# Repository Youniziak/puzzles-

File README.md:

# Chaîne « puzzle » — Exylia Project

Concevoir des cartes électroniques sans la vue : la carte est découpée en blocs par fonction, chaque bloc est routé par EasyGerber, puis la chaîne recolle et vérifie le tout avec des logiciels maintenus (KiCad 10, Freerouting, KiKit…). Elle produit aussi de quoi toucher la carte avant de la commander : plan sur papier gonflé, maquette, boîtier et banc de test à imprimer en 3D.

Dépôt public depuis le 25/10/2026. La première carte faite avec la chaîne est la radio RADIONÉO v4. Pour les questions et les idées : l'onglet Discussions.

- `METHODE-CARTES-PUZZLE.md` : la méthode, ce qui a été appris, et l'historique des versions.
- `POUR-LE-FABLAB.md` : les briques et la colle, pour quelqu'un qui voudrait aider.
- `SKILL-carte-puzzle.md` : les instructions pour l'IA qui conduit la chaîne. C'est du texte simple : chacun prend l'IA qu'il veut, libre ou non, du moment qu'elle sait lire des fichiers et lancer des commandes. La chaîne elle-même tourne sans IA. Ces instructions ont été écrites et essayées avec Claude.
- `installer-ubuntu.sh` et `Dockerfile` : pour installer les logiciels.
- `scripts/chaine.py` : la chaîne en une commande.
- `.github/workflows/kicad-happy.yml` : un deuxième avis sur chaque carte, par l'outil libre kicad-happy, à chaque changement.
- `.github/workflows/edea.yml` : un essai de l'outil libre EDeA (bibliothèque partagée de blocs KiCad) : sait-il lire nos fichiers ?

Ne sont pas dans le dépôt : les modèles 3D à imprimer (refaits par la chaîne), les schémas d'autres projets publiés, et la bibliothèque des composants de LCSC/EasyEDA (empreintes, symboles, modèles 3D), que leurs conditions interdisent de republier. Avant la première carte, chacun la télécharge chez soi :

```
python3 outils/telecharger_bibliotheque.py
```

Le script applique ensuite les retouches de la chaîne (`bibliotheque/empreintes/retouches.json`) et vérifie que les pièces n'ont pas changé chez LCSC depuis les cartes déjà faites.

## Licences

Libres et strictes : le logiciel sous GNU AGPL-3.0 (ou plus récente), le matériel (cartes, blocs, maquettes) sous CERN-OHL-S-2.0, les textes sous CC BY-SA 4.0. Le détail, et ce qui vient d'ailleurs : `LICENCE.md`. Les textes des licences : `LICENSES/`.

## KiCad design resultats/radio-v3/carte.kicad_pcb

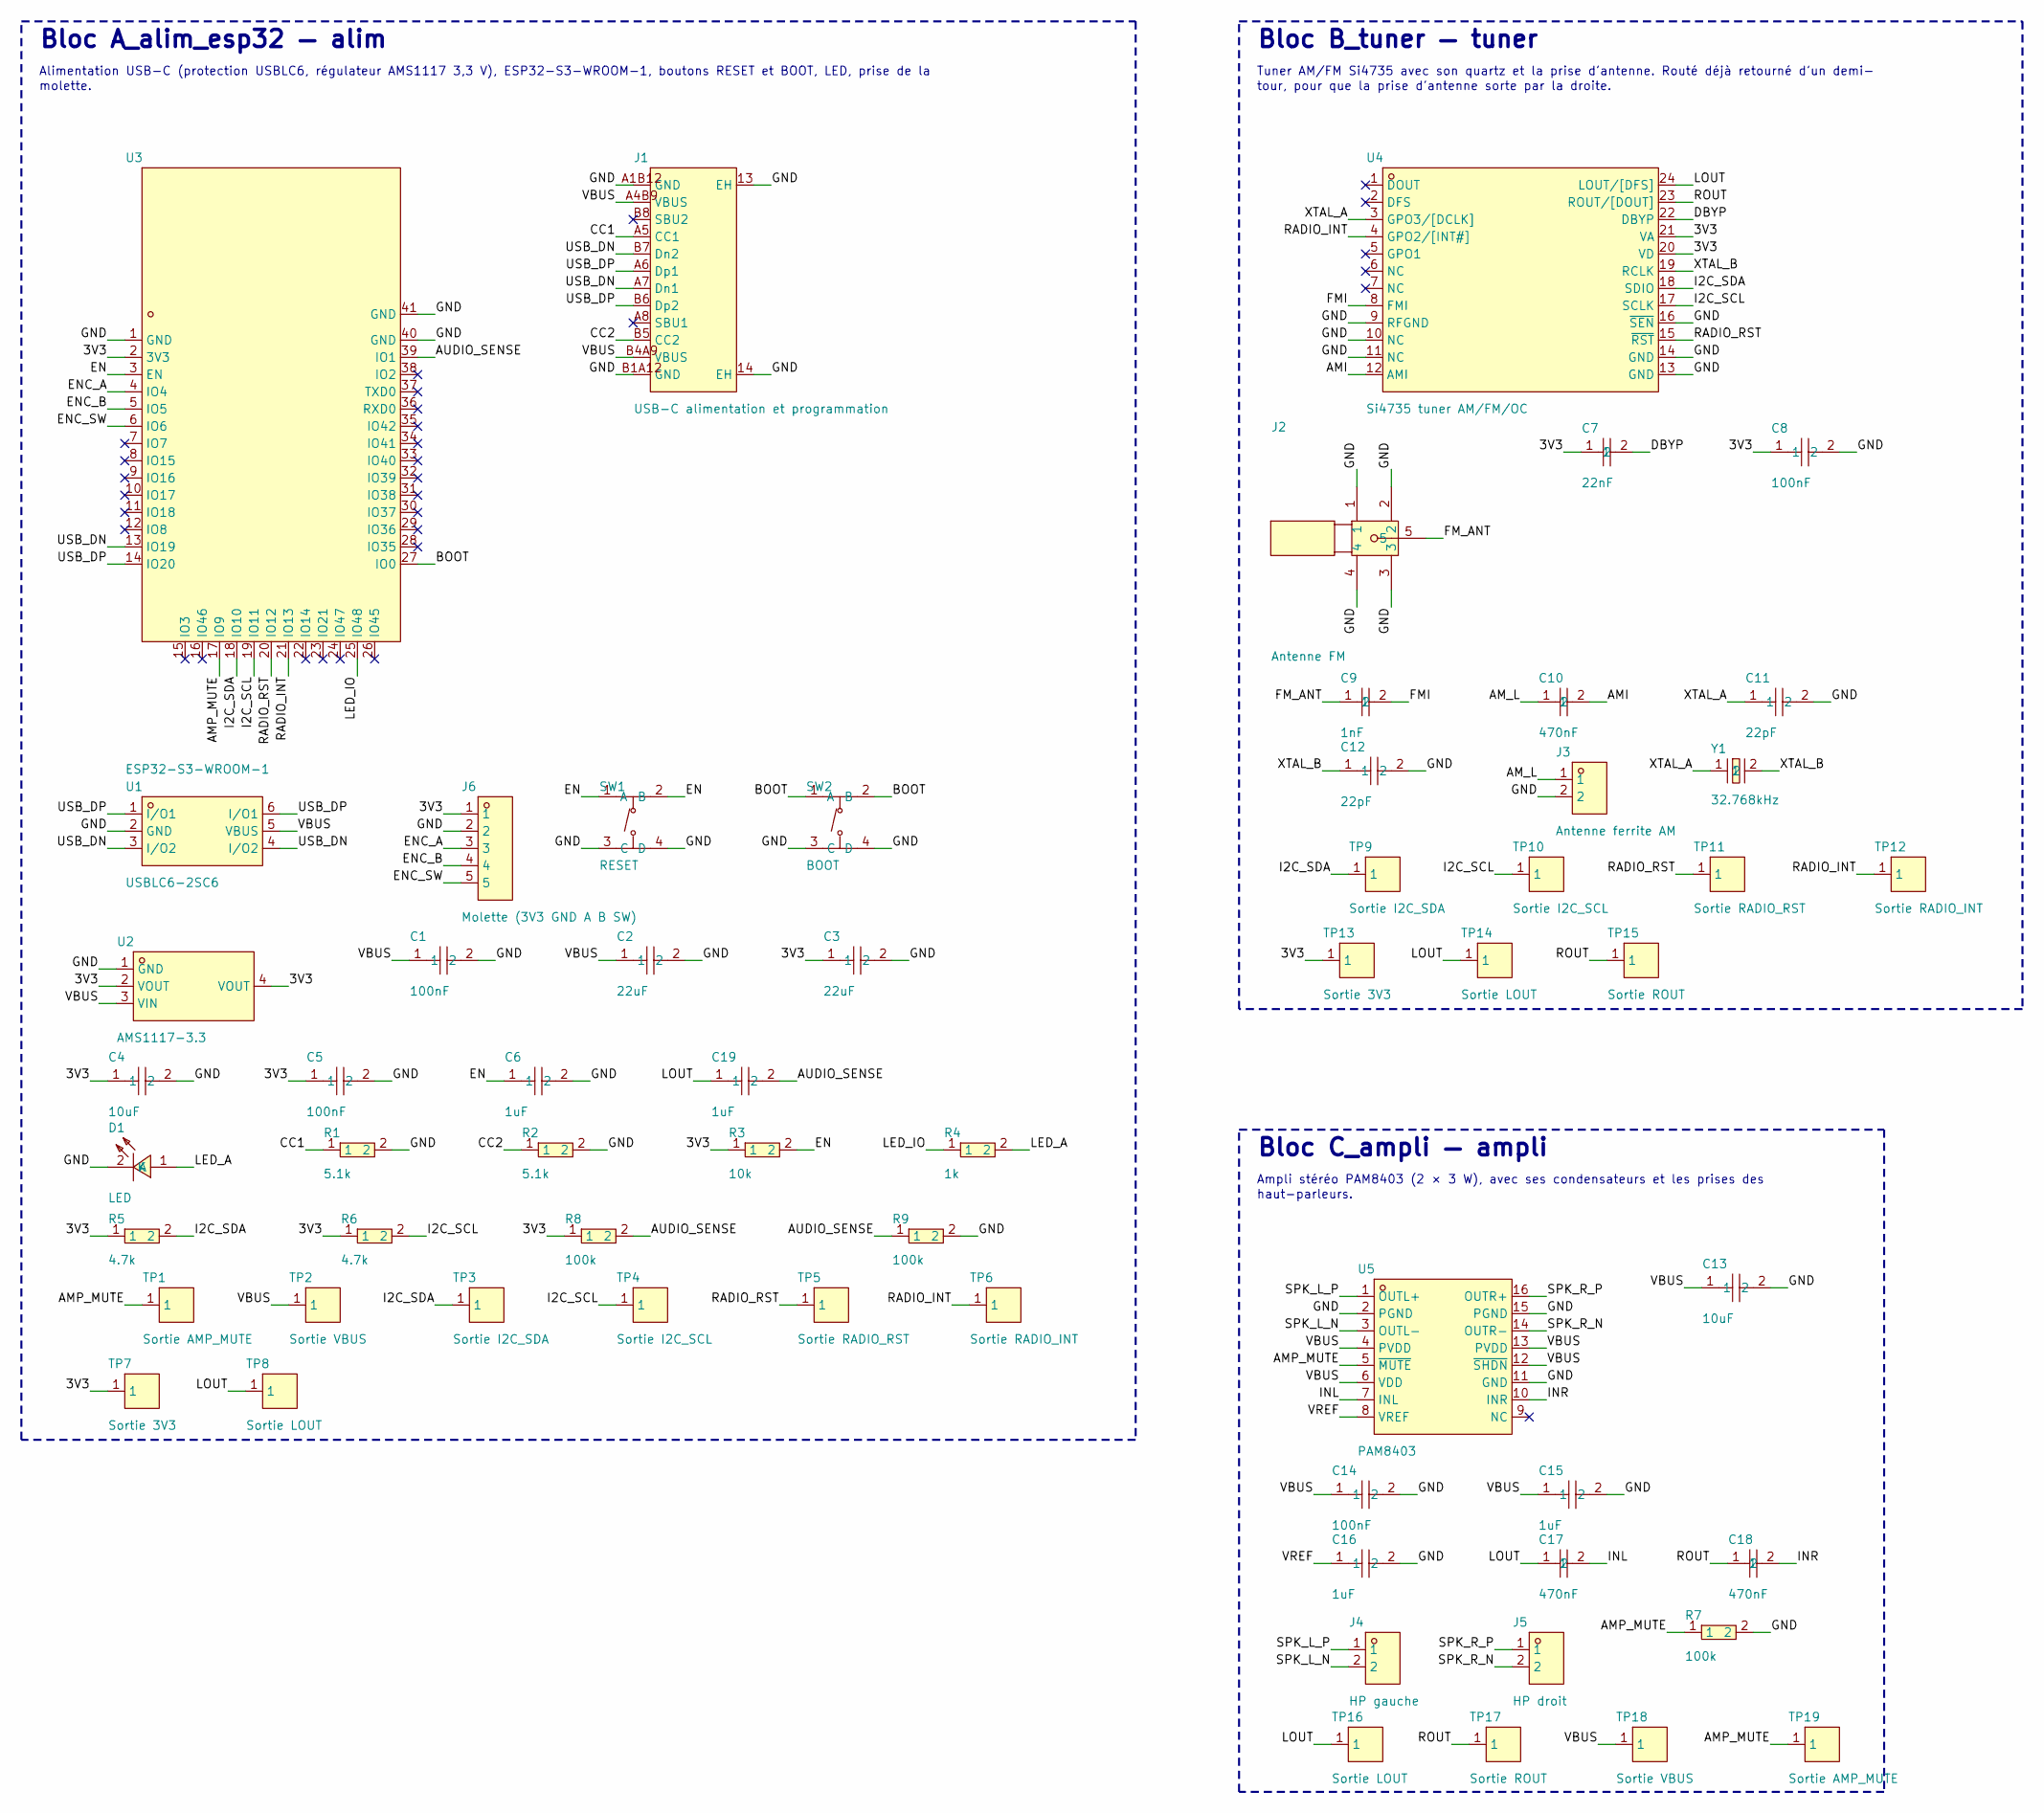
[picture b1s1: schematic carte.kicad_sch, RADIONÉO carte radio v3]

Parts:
C1, C5, C8, C14: 100nF; C0603; LCSC Part C14663
C2, C3: 22uF; C0805; LCSC Part C45783
C4, C13: 10uF; C0805; LCSC Part C440198
C6, C15, C16, C19: 1uF; C0603; LCSC Part C15849
C7: 22nF; C0603; LCSC Part C21122
C9: 1nF; C0603; LCSC Part C1588
C10, C17, C18: 470nF; C0603; LCSC Part C1623
C11, C12: 22pF; C0603; LCSC Part C1653
D1: LED; LED-SMD_L1.6-W0.8-R-RD; LCSC Part C2286
J1: USB-C alimentation et programmation; USB-C-SMD_TYPE-C-16PIN-2MD-073; LCSC Part C2765186
J2: Antenne FM; SMA-TH_SMA-RA-132135; LCSC Part C5183768
J3: Antenne ferrite AM; HDR-TH_2P-P2.54-V-M; LCSC Part C492401
J4: HP gauche; HDR-TH_2P-P2.54-V-M; LCSC Part C492401
J5: HP droit; HDR-TH_2P-P2.54-V-M; LCSC Part C492401
J6: Molette (3V3 GND A B SW); HDR-TH_5P-P2.54-V-M; LCSC Part C492404
R1, R2: 5.1k; R0603; LCSC Part C23186
R3: 10k; R1206; LCSC Part C17902
R4: 1k; R0603; LCSC Part C21190
R5, R6: 4.7k; R0603; LCSC Part C23162
R7, R8, R9: 100k; R0603; LCSC Part C25803
SW1: RESET; SW-SMD_4P-L5.1-W5.1-P3.70-LS6.5-TL_H1.5; LCSC Part C318884
SW2: BOOT; SW-SMD_4P-L5.1-W5.1-P3.70-LS6.5-TL_H1.5; LCSC Part C318884
TP1, TP19: Sortie AMP_MUTE; SMD_RH-5015; LCSC Part C5199798
TP2, TP18: Sortie VBUS; SMD_RH-5015; LCSC Part C5199798
TP3, TP9: Sortie I2C_SDA; SMD_RH-5015; LCSC Part C5199798
TP4, TP10: Sortie I2C_SCL; SMD_RH-5015; LCSC Part C5199798
TP5, TP11: Sortie RADIO_RST; SMD_RH-5015; LCSC Part C5199798
TP6, TP12: Sortie RADIO_INT; SMD_RH-5015; LCSC Part C5199798
TP7, TP13: Sortie 3V3; SMD_RH-5015; LCSC Part C5199798
TP8, TP14, TP16: Sortie LOUT; SMD_RH-5015; LCSC Part C5199798
TP15, TP17: Sortie ROUT; SMD_RH-5015; LCSC Part C5199798
U1: USBLC6-2SC6; SOT-23-6_L2.9-W1.6-P0.95-LS2.8-BL; LCSC Part C2687116
U2: AMS1117-3.3; SOT-223-3_L6.5-W3.4-P2.30-LS7.0-BR; LCSC Part C6186
U3: ESP32-S3-WROOM-1; WIRELM-SMD_ESP32-S3-WROOM-1; LCSC Part C2913202
U4: Si4735 tuner AM/FM/OC; SSOP-24_L8.7-W3.9-P0.64-LS6.0-BL; LCSC Part C1526089
U5: PAM8403; SOP-16_L10.0-W3.9-P1.27-LS6.0-BL; LCSC Part C5122557
Y1: 32.768kHz; CRYSTAL-SMD_L3.2-W1.5-1; LCSC Part C5361379

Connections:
3V3: C3.1, C4.1, C5.1, C7.1, C8.1, J6.1, R3.1, R5.1, R6.1, R8.1, TP7.1, TP13.1, U2.2 (VOUT), U2.4 (VOUT), U3.2 (3V3), U4.20 (VD), U4.21 (VA)
AMI: C10.2, U4.12 (AMI)
AMP_MUTE: R7.1, TP1.1, TP19.1, U3.17 (IO9), U5.5 (~MUTE)
AM_L: C10.1, J3.1
AUDIO_SENSE: C19.2, R8.2, R9.1, U3.39 (IO1)
BOOT: SW2.1 (A), SW2.2 (B), U3.27 (IO0)
CC1: J1.A5 (CC1), R1.1
CC2: J1.B5 (CC2), R2.1
DBYP: C7.2, U4.22 (DBYP)
EN: C6.1, R3.2, SW1.1 (A), SW1.2 (B), U3.3 (EN)
ENC_A: J6.3, U3.4 (IO4)
ENC_B: J6.4, U3.5 (IO5)
ENC_SW: J6.5, U3.6 (IO6)
FMI: C9.2, U4.8 (FMI)
FM_ANT: C9.1, J2.5
GND: C1.2, C2.2, C3.2, C4.2, C5.2, C6.2, C8.2, C11.2, C12.2, C13.2, C14.2, C15.2, C16.2, D1.2 (K), J1.13 (EH), J1.14 (EH), J1.A1B12 (GND), J1.B1A12 (GND), J2.1, J2.2, J2.3, J2.4, J3.2, J6.2, R1.2, R2.2, R7.2, R9.2, SW1.3 (C), SW1.4 (D), SW2.3 (C), SW2.4 (D), U1.2 (GND), U2.1 (GND), U3.1 (GND), U3.40 (GND), U3.41 (GND), U4.9 (RFGND), U4.10 (NC), U4.11 (NC), U4.13 (GND), U4.14 (GND), U4.16 (~SEN), U5.2 (PGND), U5.11 (GND), U5.15 (PGND)
I2C_SCL: R6.2, TP4.1, TP10.1, U3.19 (IO11), U4.17 (SCLK)
I2C_SDA: R5.2, TP3.1, TP9.1, U3.18 (IO10), U4.18 (SDIO)
INL: C17.2, U5.7 (INL)
INR: C18.2, U5.10 (INR)
LED_A: D1.1 (A), R4.2
LED_IO: R4.1, U3.25 (IO48)
LOUT: C17.1, C19.1, TP8.1, TP14.1, TP16.1, U4.24 (LOUT/[DFS])
RADIO_INT: TP6.1, TP12.1, U3.21 (IO13), U4.4 (GPO2/[INT#])
RADIO_RST: TP5.1, TP11.1, U3.20 (IO12), U4.15 (~RST)
ROUT: C18.1, TP15.1, TP17.1, U4.23 (ROUT/[DOUT])
SPK_L_N: J4.2, U5.3 (OUTL-)
SPK_L_P: J4.1, U5.1 (OUTL+)
SPK_R_N: J5.2, U5.14 (OUTR-)
SPK_R_P: J5.1, U5.16 (OUTR+)
USB_DN: J1.A7 (Dn1), J1.B7 (Dn2), U1.3 (I/O2), U1.4 (I/O2), U3.13 (IO19)
USB_DP: J1.A6 (Dp1), J1.B6 (Dp2), U1.1 (I/O1), U1.6 (I/O1), U3.14 (IO20)
VBUS: C1.1, C2.1, C13.1, C14.1, C15.1, J1.A4B9 (VBUS), J1.B4A9 (VBUS), TP2.1, TP18.1, U1.5 (VBUS), U2.3 (VIN), U5.4 (PVDD), U5.6 (VDD), U5.12 (~SHDN), U5.13 (PVDD)
VREF: C16.1, U5.8 (VREF)
XTAL_A: C11.1, U4.3 (GPO3/[DCLK]), Y1.1
XTAL_B: C12.1, U4.19 (RCLK), Y1.2

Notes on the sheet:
Bloc A_alim_esp32 — alim
Alimentation USB-C (protection USBLC6, régulateur AMS1117 3,3 V), ESP32-S3-WROOM-1, boutons RESET et BOOT, LED, prise de la
molette.
Bloc B_tuner — tuner
Tuner AM/FM Si4735 avec son quartz et la prise d'antenne. Routé déjà retourné d'un demi-
tour, pour que la prise d'antenne sorte par la droite.
Bloc C_ampli — ampli
Ampli stéréo PAM8403 (2 × 3 W), avec ses condensateurs et les prises des
haut-parleurs.

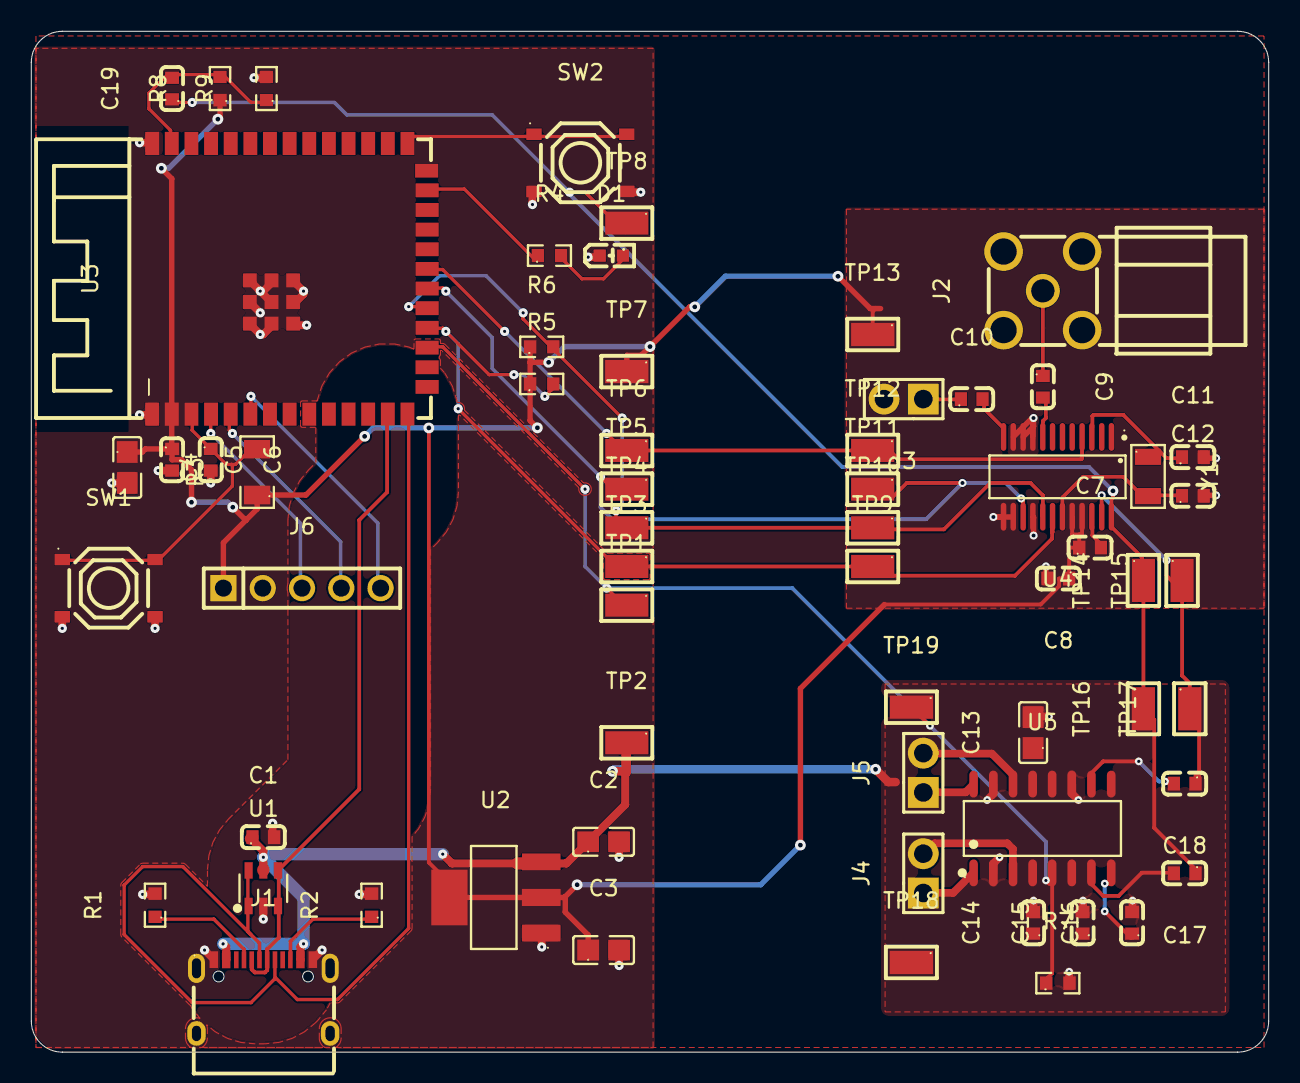
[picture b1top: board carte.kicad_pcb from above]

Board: 2 copper layers, 80.0 x 66.0 mm, 62 parts (0 on the bottom side), 36 nets.

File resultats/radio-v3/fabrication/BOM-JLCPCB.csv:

"Comment","Designator","Footprint","LCSC Part #","MPN","Manufacturer"
"USB-C alimentation et programmation -25℃~+85℃ 1 16P 3A 5,000 times 5V Black Female Surface Mount, Right Angle Type-C SMD USB Connectors ROHS Application guidance for a USB 2.0, fixed 5 V sink without USB Power Delivery: when no controller already provides Rd, connect CC1 and CC2 each through its own nominal 5.1 kΩ Rd resistor to GND; keep CC1 and CC2 as separate nets. Source: TI SLVSF62B, Sep2021, §10.3.16.2 and Fig10-14, pp35–36: https://www.ti.com/mx/lit/gpn/tps25859-q1.","J1","SMD","C2765186","TYPE-C 16PIN 2MD(073)","SHOU HAN"
"5.1k -55℃~+155℃ 100mW 5.1kΩ 75V Thick Film Resistor ±1% ±100ppm/℃ 0603 Chip Resistor - Surface Mount ROHS","R1, R2","0603","C23186","0603WAF5101T5E","UNI-ROYAL(Uniroyal Elec)"
"USBLC6-2SC6 0.35pF、0.8pF 100nA 150W@8/20us 15V 2 5V 6A@8/20us 6V ESD SOT-23-6 ESD and Surge Protection (TVS/ESD) ROHS UMW USBLC6-2SC6 application facts: passive two-line ESD protection for USB 2.0, with 5 V operating voltage. Pins 1 and 6 share I/O1; pins 3 and 4 share I/O2; pin 2 is GND; pin 5 is VBUS. For a 5 V USB application, connect pin 5 to VBUS and pin 2 to GND; keep each I/O pair on one data signal and the other pair on the other data signal. Source: UMW USBLC6-2SC6, Nov 2024, p1 sections 1, 2 and 4, p3 section 6: https://www.umw-ic.com/static/pdf/b2c190f0a00a742e1ffd3347f2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","U1","SOT-23-6","C2687116","USBLC6-2SC6","UMW(Youtai Semiconductor Co., Ltd.)"
"100nF 100nF 50V X7R ±10% 0603 Multilayer Ceramic Capacitors MLCC - SMD/SMT ROHS","C1, C5, C8, C14","0603","C14663","CC0603KRX7R9BB104","Yageo"
"AMS1117-3.3 -40℃~+125℃ 0.003%Vout 1 1.1V@(800mA) 15V 1A 3.3V 5mA 72dB@(120Hz) Fixed Over Current Protection、Thermal Shutdown Positive SOT-223 Voltage Regulators - Linear, Low Drop Out (LDO) Regulators ROHS","U2","SOT-223","C6186","AMS1117-3.3","Advanced Monolithic Systems"
"22uF 22uF 25V X5R ±20% 0805 Multilayer Ceramic Capacitors MLCC - SMD/SMT ROHS","C2, C3","0805","C45783","CL21A226MAQNNNE","Samsung Electro-Mechanics"
"ESP32-S3-WROOM-1 -103.5dBm -40℃~+65℃ 2.4GHz 20.5dBm 355mA 3V~3.6V 95mA ESP32-S3R8 On-board PCB Antenna UART、SPI、I2C、GPIO、I2S、USB SMD,25.5x18mm WiFi Modules ROHS","U3","SMD,25.5x18mm","C2913202","ESP32-S3-WROOM-1-N16R8","Espressif Systems"
"10uF 10uF 50V X5R ±10% 0805 Multilayer Ceramic Capacitors MLCC - SMD/SMT ROHS","C4, C13","0805","C440198","GRM21BR61H106KE43L","Murata Electronics"
"10k -55℃~+155℃ 10kΩ 200V 250mW Thick Film Resistor ±1% ±100ppm/℃ 1206 Chip Resistor - Surface Mount ROHS","R3","1206","C17902","1206W4F1002T5E","UNI-ROYAL(Uniroyal Elec)"
"1uF 1uF 50V X5R ±10% 0603 Multilayer Ceramic Capacitors MLCC - SMD/SMT ROHS","C19, C6, C15, C16","0603","C15849","CL10A105KB8NNNC","Samsung Electro-Mechanics"
"RESET -30℃~+85℃ 1.5mm 1.6N 100,000 cycles 12V 5.1mm 5.1mm 50mA Gold No Round Button SPST Surface Mount,Vertical Without Bracket SMD-4P,5.1x5.1mm Tactile Switches ROHS","SW1, SW2","SMD-4P,5.1x5.1mm","C318884","TS-1187A-B-A-B","XKB Connection"
"1k -55℃~+155℃ 100mW 1kΩ 75V Thick Film Resistor ±1% ±100ppm/℃ 0603 Chip Resistor - Surface Mount ROHS","R4","0603","C21190","0603WAF1001T5E","UNI-ROYAL(Uniroyal Elec)"
"LED -40℃~+85℃ 1.8V~2.4V 120° 20mA 300mcd 40mW 615nm~630nm 645nm Discrete Diode Red Water Clear 0603 LED Indication - Discrete ROHS","D1","0603","C2286","KT-0603R","Hubei KENTO Elec"
"4.7k -55℃~+155℃ 100mW 4.7kΩ 75V Thick Film Resistor ±1% ±100ppm/℃ 0603 Chip Resistor - Surface Mount ROHS","R5, R6","0603","C23162","0603WAF4701T5E","UNI-ROYAL(Uniroyal Elec)"
"100k -55℃~+155℃ 100kΩ 100mW 75V Thick Film Resistor ±1% ±100ppm/℃ 0603 Chip Resistor - Surface Mount ROHS","R8, R9, R7","0603","C25803","0603WAF1003T5E","UNI-ROYAL(Uniroyal Elec)"
"Molette (3V3 GND A B SW) -40℃~+105℃ 1 1x5P 2.54mm 2.5mm 250V 3A 3mm 5P 6mm Black Brass Pin Header Through Hole 插件,P=2.54mm Pin Headers ROHS","J6","Plugin,P=2.54mm","C492404","PZ254V-11-05P","XFCN"
"Si4735 tuner AM/FM/OC -20℃~+85℃ 153kHz~279kHz、520kHz~1.71MHz、2.3MHz~26.1MHz、64MHz~108MHz 2.7V~5.5V Receivers SPI、I2C SSOP-24-150mil RF Transceiver ICs ROHS","U4","SSOP-24-150mil","C1526089","SI4735-D60-GU","SKYWORKS/SILICON LABS"
"32.768kHz -40℃~+85℃ 12.5pF 32.768kHz 70kΩ Crystal Oscillator ±20ppm ±30ppm SMD3215-2P Crystals ROHS","Y1","SMD3215-2P","C5361379","H31003271C2070CY","JGHC"
"22pF 22pF 50V C0G ±5% 0603 Multilayer Ceramic Capacitors MLCC - SMD/SMT ROHS","C11, C12","0603","C1653","CL10C220JB8NNNC","Samsung Electro-Mechanics"
"22nF 22nF 50V X7R ±10% 0603 Multilayer Ceramic Capacitors MLCC - SMD/SMT ROHS","C7","0603","C21122","CL10B223KB8NNNC","Samsung Electro-Mechanics"
"Antenne FM 1 12.4GHz 50Ω Connector SMA SMA-RA-132135 Coaxial Connectors (RF) ROHS","J2","SMA-RA-132135","C5183768","132135","Amphenol"
"1nF 1nF 50V X7R ±10% 0603 Multilayer Ceramic Capacitors MLCC - SMD/SMT ROHS","C9","0603","C1588","CL10B102KB8NNNC","Samsung Electro-Mechanics"
"470nF 25V 470nF X7R ±10% 0603 Multilayer Ceramic Capacitors MLCC - SMD/SMT ROHS","C10, C17, C18","0603","C1623","CL10B474KA8NNNC","Samsung Electro-Mechanics"
"Antenne ferrite AM -40℃~+105℃ 1 1x2P 2.54mm 2.5mm 250V 2P 3A 3mm 6mm Black Brass Pin Header Through Hole 插件,P=2.54mm Pin Headers ROHS","J3, J4, J5","Plugin,P=2.54mm","C492401","PZ254V-11-02P","XFCN"
"PAM8403 -40℃~+85℃ 2-Channel 2.2V~5.5V 3Wx2@4Ω 6.3mA 90% Automatic mute/no-noise switch、Enable/disable function、Filterless architecture Class D SOP-16 Audio Amplifiers ROHS","U5","SOP-16","C5122557","PAM8403","Slkor(SLKORMICRO Elec.)"

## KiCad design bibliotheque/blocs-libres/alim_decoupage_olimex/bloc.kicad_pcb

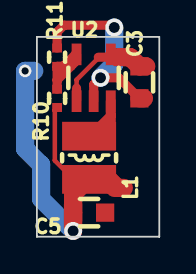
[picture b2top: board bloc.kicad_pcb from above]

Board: 2 copper layers, 6.8 x 11.1 mm, 6 parts (0 on the bottom side), 5 nets.

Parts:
C3, C5: 22uF/6.3V/20%/X5R/C0603; C_0603_5MIL_DWS
L1: 2.2uH/1.5A/DCR=72mR/20%/3.00x3.00x1.50mm/CD32(NR3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; CD32
R10: 220k/R0402; R_0402_5MIL_DWS
R11: 49.9k/1%/R0402; R_0402_5MIL_DWS
U2: SY8089AAAC(SOT23-5); SOT-23-5

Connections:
3V3: C5.1, L1.2, R10.2
DCDC_FB: R10.1, R11.1, U2.5
DCDC_SW: L1.1, U2.3
GND: C3.2, C5.2, R11.2, U2.2
VBUS: C3.1, U2.1, U2.4

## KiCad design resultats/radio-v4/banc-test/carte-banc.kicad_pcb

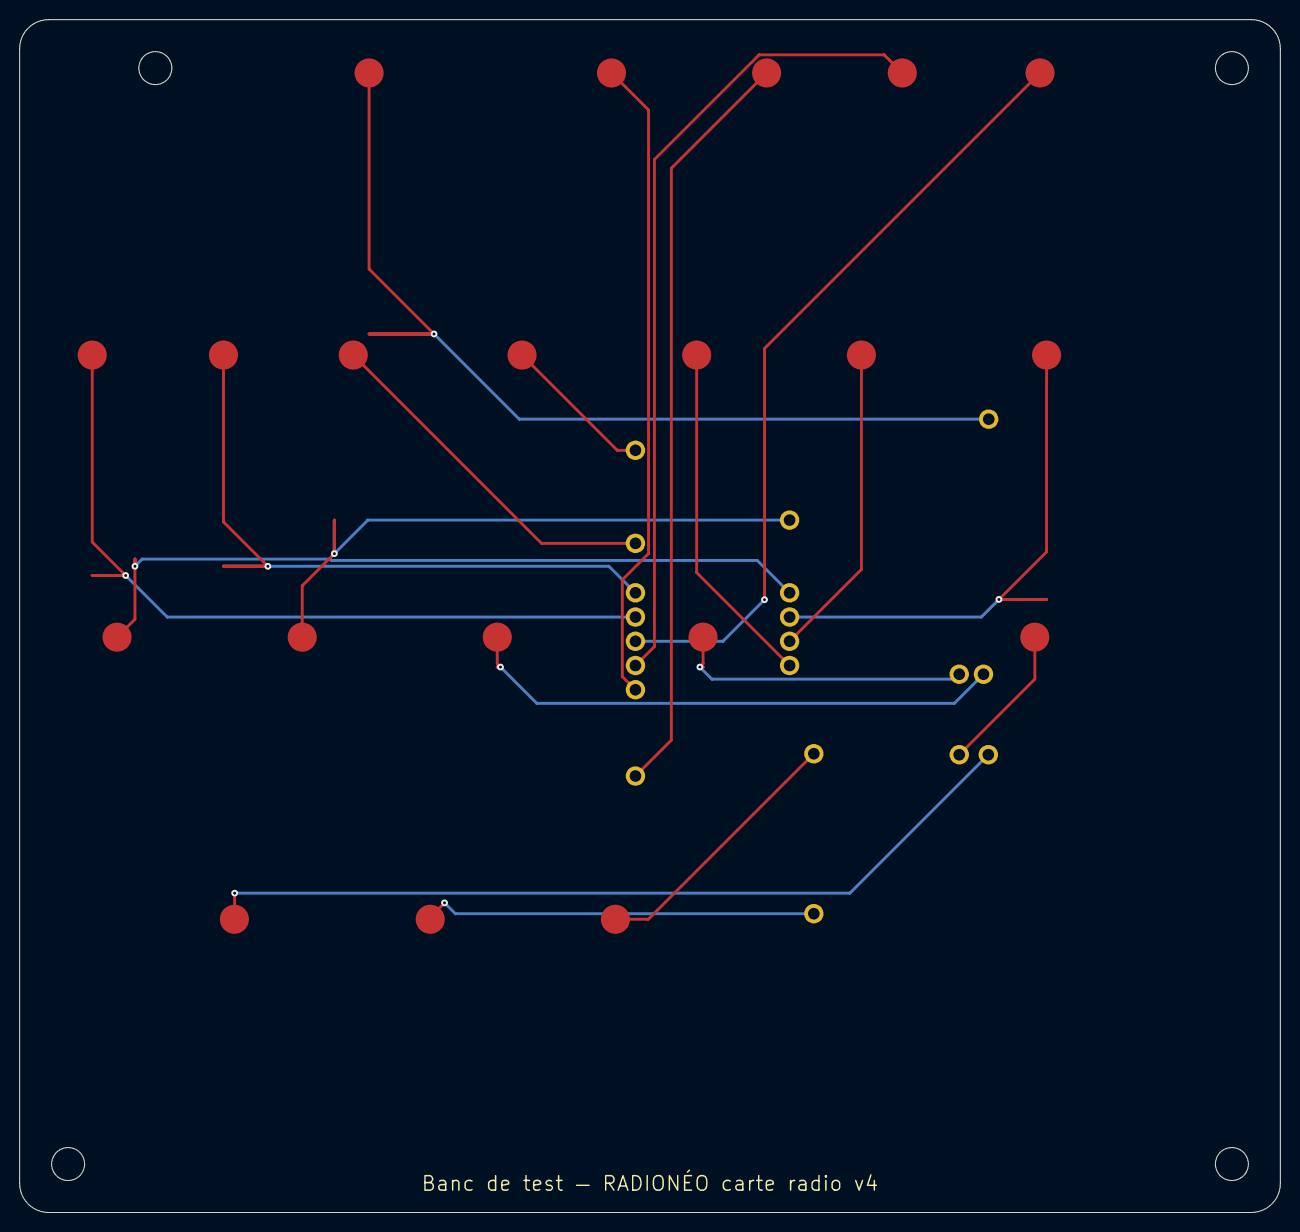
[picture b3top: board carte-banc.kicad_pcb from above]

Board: 2 copper layers, 130.1 x 123.0 mm, 44 parts (0 on the bottom side), 20 nets.

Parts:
B1: borne masse; Borne_ronde
B2: borne 1; Borne_ronde
B3: borne 2; Borne_ronde
B4: borne 3; Borne_ronde
B5: borne 4; Borne_ronde
B6: borne 5; Borne_ronde
B7: borne 6; Borne_ronde
B8: borne 7; Borne_ronde
B9: borne 8; Borne_ronde
B10: borne 9; Borne_ronde
B11: borne 10; Borne_ronde
B12: borne 11; Borne_ronde
B13: borne 12; Borne_ronde
B14: borne 13; Borne_ronde
B15: borne 14; Borne_ronde
B16: borne 15; Borne_ronde
B17: borne 16; Borne_ronde
B18: borne 17; Borne_ronde
B19: borne 18; Borne_ronde
B20: borne 19; Borne_ronde
P1, P2, P3, P4, P5, P6, P7, P8, P9, P10, P11, P12, P13, P14, P15, P16, P17, P18, P19, P20: P75-E2; Pointe_P75
V1, V2, V3, V4: trou de vis M3; Trou_vis

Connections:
MASSE: B1.1, P1.1
TP1: B2.1, P2.1
TP2: B3.1, P3.1
TP3: B4.1, P4.1
TP4: B5.1, P5.1
TP5: B6.1, P6.1
TP6: B7.1, P7.1
TP7: B8.1, P8.1
TP8: B9.1, P9.1
TP9: B10.1, P10.1
TP10: B11.1, P11.1
TP11: B12.1, P12.1
TP12: B13.1, P13.1
TP13: B14.1, P14.1
TP14: B15.1, P15.1
TP15: B16.1, P16.1
TP16: B17.1, P17.1
TP17: B18.1, P18.1
TP18: B19.1, P19.1
TP19: B20.1, P20.1
